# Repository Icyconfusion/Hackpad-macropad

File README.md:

# Hackpad-macropad
A small macropad based off of Blueprint Hackclub's hackpad guide. It has 2x EC11 rotary encoders, 14x switches, and an oled screen. based off the XIAO rp2040 DIP. 

The left rotary encoder is used to cycle through 3 layers, creating 54 unique outputs from just 16 physical inputs. The firmware was very difficult on QMK, as I used charlieplexing in the wiring. The case comes in two parts, a base, which the pcb sits inside, and a top plate which sits on top and is held in by screws. 

The case assembles as so:

Schematic:

PCB:

BOM:
14x Cherry MX switches
2x EC11 rotary encoders
1x 0.91" 128x32 SSD1306 Oled display
1x XIAO RP2040
1x PCB
14x Blank DSA Keycaps
4x M3x16 Bolt
4x M3 Heatset

During the prject I had to solve the issue of not having enough pins to fit all the buttons. This led me to trying a button matrix, but instead I chose charlieplexing as the more appropriate method to fit the buttons. I then decided, to increase the outputs, I should introduce layers to the macropad in QMK. This part of the QMK firmware was quite easy, but it took many, many hours attempting to solve the problems that arose from charlieplexing.
A massive thank you to Hackclub blueprint for this project and their guidance on the Hackpad project.

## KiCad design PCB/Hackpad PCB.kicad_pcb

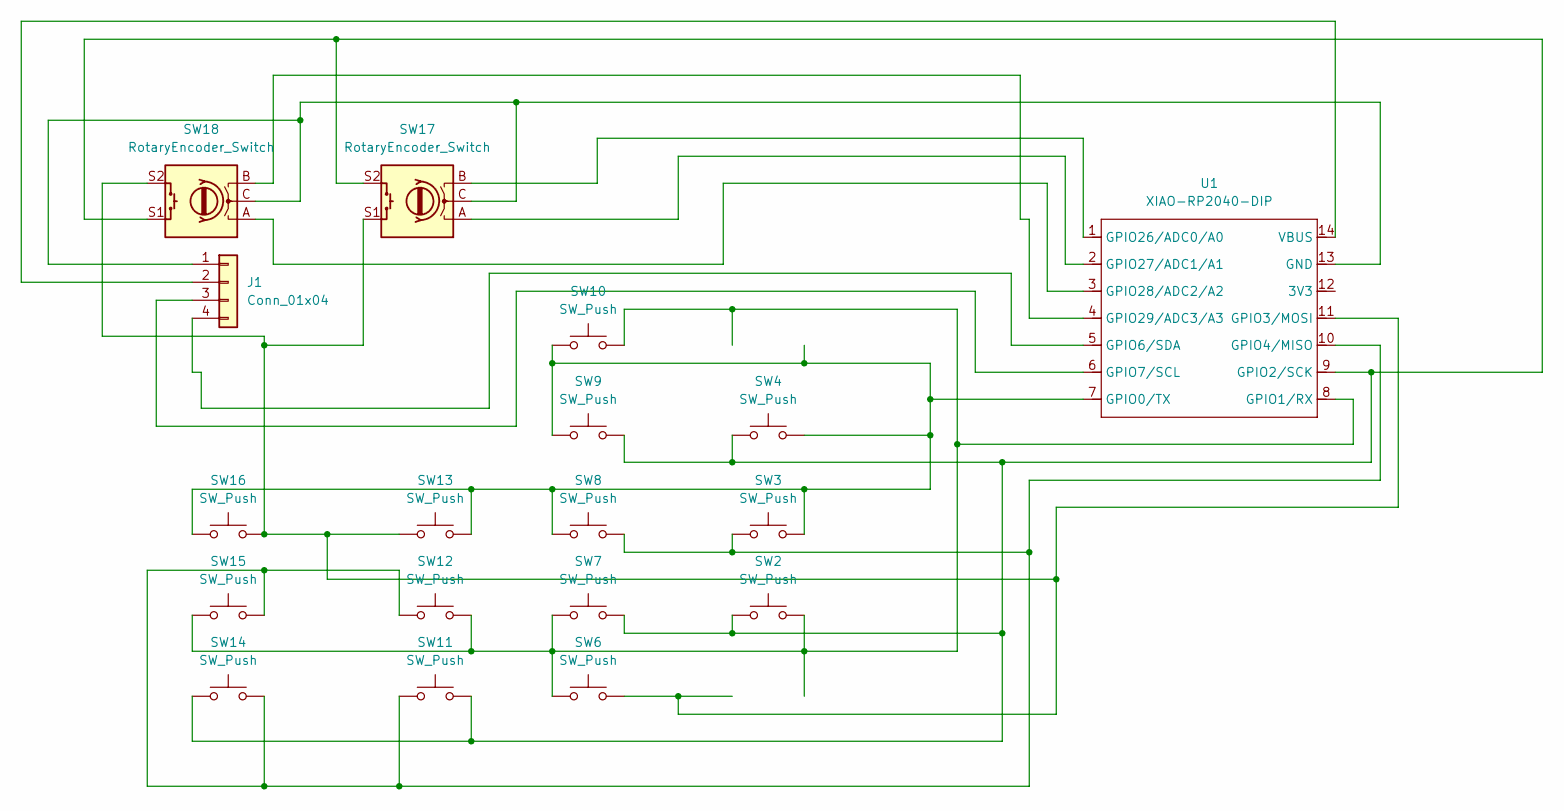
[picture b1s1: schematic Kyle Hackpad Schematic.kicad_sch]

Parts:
J1: Conn_01x04; PinHeader_1x04_P2.54mm_Vertical
SW2, SW3, SW4, SW6, SW7, SW8, SW9, SW10, SW11, SW12, SW13, SW14, SW15, SW16: SW_Push; SW_Cherry_MX_1.00u_PCB
SW17, SW18: RotaryEncoder_Switch; RotaryEncoder_Alps_EC11E-Switch_Vertical_H20mm
U1: XIAO-RP2040-DIP

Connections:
unnamed: J1.1, SW17.C, SW18.C, U1.13 (GND)
unnamed: J1.2, U1.14 (VBUS)
unnamed: J1.3, U1.6 (GPIO7/SCL)
unnamed: J1.4, U1.5 (GPIO6/SDA)
unnamed: SW3.2, SW4.2, SW8.1, SW9.1, SW10.1, SW13.2, SW16.1, U1.7 (GPIO0/TX)
unnamed: SW2.2, SW6.1, SW7.1, SW10.2, SW12.2, SW15.1, U1.8 (GPIO1/RX)
unnamed: SW2.1, SW4.1, SW7.2, SW9.2, SW11.2, SW14.1, SW17.S2, SW18.S1, U1.9 (GPIO2/SCK)
unnamed: SW6.2, SW13.1, SW16.2, SW17.S1, SW18.S2, U1.11 (GPIO3/MOSI)
unnamed: SW3.1, SW8.2, SW11.1, SW12.1, SW14.2, SW15.2, U1.10 (GPIO4/MISO)
unnamed: SW17.B, U1.1 (GPIO26/ADC0/A0)
unnamed: SW17.A, U1.2 (GPIO27/ADC1/A1)
unnamed: SW18.A, U1.3 (GPIO28/ADC2/A2)
unnamed: SW18.B, U1.4 (GPIO29/ADC3/A3)

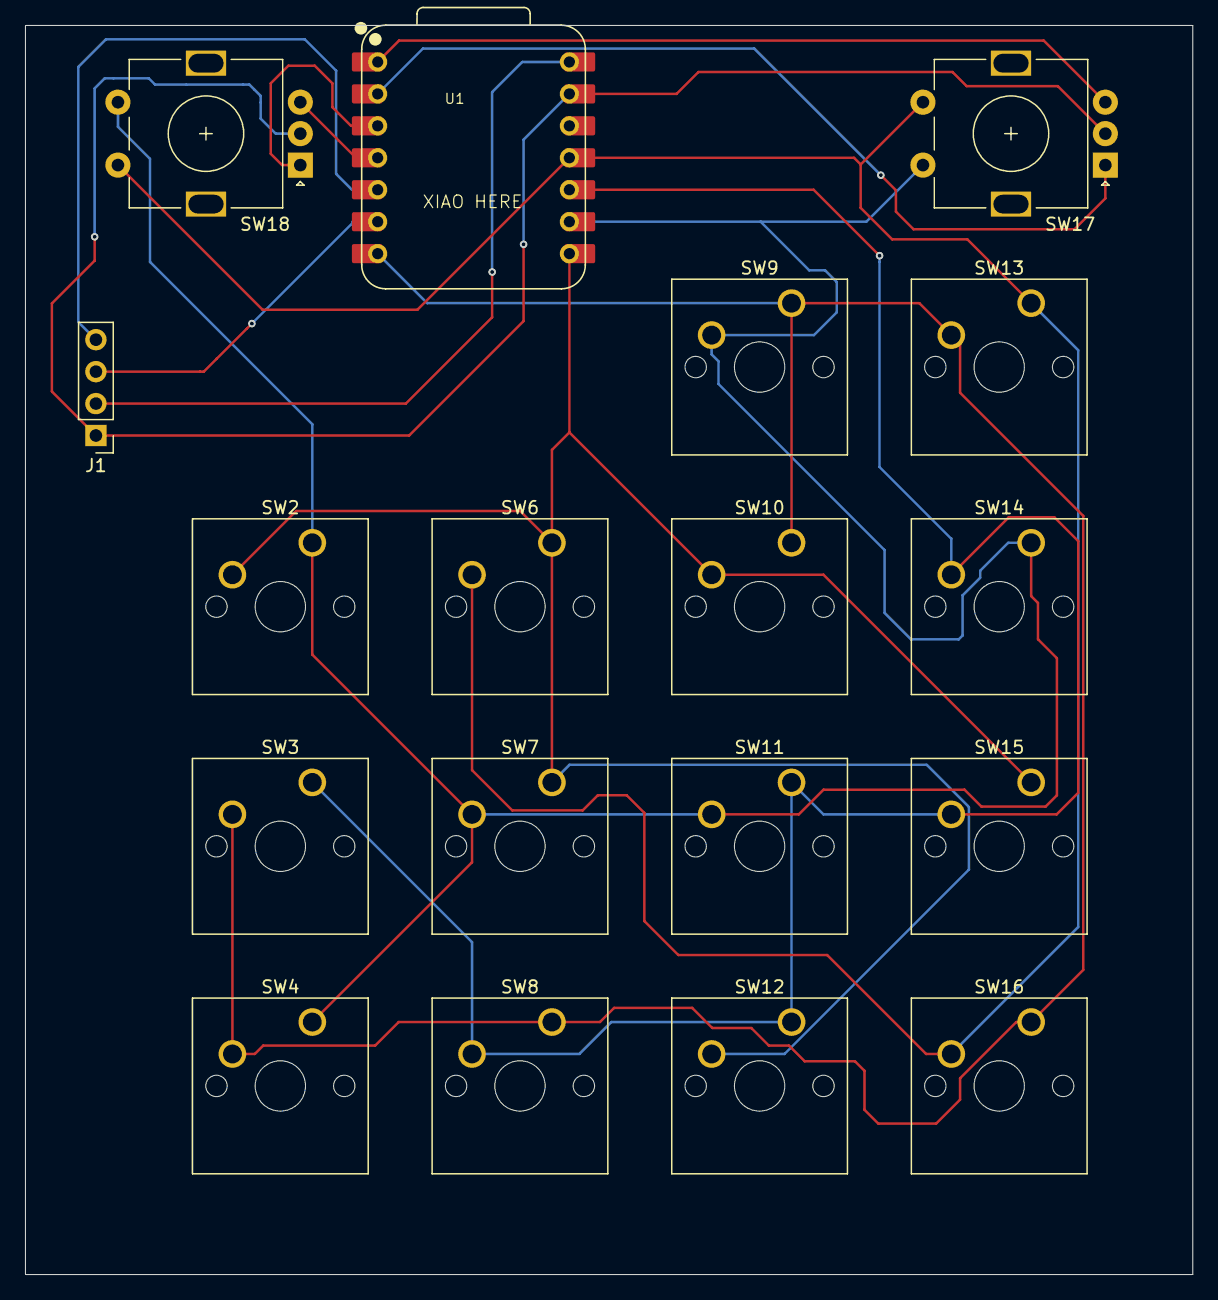
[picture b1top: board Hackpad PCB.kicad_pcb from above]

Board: 2 copper layers, 92.8 x 99.3 mm, 18 parts (0 on the bottom side), 13 nets.

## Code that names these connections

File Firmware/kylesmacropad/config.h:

#pragma once

#include "config_common.h"

// Matrix size: 4 rows × 4 cols (16 buttons)
#define MATRIX_ROWS 4
#define MATRIX_COLS 4

// Charlieplex pins: P1=GPIO0, P2=GPIO1, P3=GPIO2, P4=GPIO4, P5=GPIO3
#define CHARLIE_PINS { GP0, GP1, GP2, GP4, GP3 }
#define NUM_CHARLIE_PINS 5

// Encoder pins (A and B for each)
#define ENCODER_LEFT_A GP28
#define ENCODER_LEFT_B GP29
#define ENCODER_RIGHT_A GP26
#define ENCODER_RIGHT_B GP27

// I2C pins for OLED SSD1306 128x32
#define OLED_SDA_PIN GP6
#define OLED_SCL_PIN GP7

// Layers
#define _SCHOOLWORK 0
#define _RACING     1
#define _GENERAL    2

// USB Device descriptor parameters
#define VENDOR_ID       0xFEED
#define PRODUCT_ID      0x6060
#define DEVICE_VER      0x0001
#define MANUFACTURER    Kyle Mason
#define PRODUCT         KylesMacropad

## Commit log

2025-12-03 Completed project
    Added all necessary files including CAD, Firmware and PCB folders. Edited readme and added photos.
